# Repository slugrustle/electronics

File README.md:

# Electronics

This repository includes various electronics projects in a sufficient state of completion to publish informally.

HighImpedanceBuffer is a two&#x2011;channel unity gain buffer amplifier with high impedance inputs and a &#xb1;17.5V input range.

SOT23ZenerTester is a fixture and set of software that can be used to obtain the voltage / current curves of SOT23&#x2011;3 case Zener diodes when used in conjunction with other test equipment.

TestSequencer is a fairly simple board that surrounds an 8&#x2011;bit PIC microcontroller with a power supply, programming header, and various inputs and outputs through ESD protected terminal blocks. I use it for controlling other equipment and running tests.

HH509R\_Logger is a command line program to log temperature measurements from an Omega Engineering HH509R thermocouple reader.

Big\_Fast\_Switch is a sizable combination of film capacitor, N-MOSFET, and rectifier intended for generating input voltage transients to test DC->DC converters.

## Getting Started

The README files the individual directories descibed above are a good place to start.

## Contributing

I would love to receive bug reports and user feedback. If you have improvements to the code, please get in touch.

## Author

Ben Tesch &#x2013; [slugrustle](https://github.com/slugrustle)

## License

All files in this repository that have been produced by the author are distributed under the [CC0 1.0 Universal Public Domain Dedication](https://creativecommons.org/publicdomain/zero/1.0/). See also LICENSE.txt in each project directory and the files themselves.

The projects in this repository store copies of datasheets for parts used in each project. These remain under the copyright of their respective owners and are provided for reference.

The SOT23ZenerTester project also includes copies of files from the redistributable software for the Diolan DLN&#x2011;4ME interface adapter. These files belong to Diolan; see https://diolan.com for more information.

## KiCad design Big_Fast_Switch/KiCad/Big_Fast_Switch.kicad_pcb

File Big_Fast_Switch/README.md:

## Big\_Fast\_Switch

This project is a single-board assembly containing the following power electronic devices

- Large, high-voltage film capacitor (B32756G8156K000)
- High-voltage, low Rds(on), wide SOA N-Channel MOSFET (STY145N65M5)
- High-voltage, high-current fast rectifier (VS-90EPF06L-M3)

and the following support electronics / devices

- An isolated gate driver for the N-MOSFET
- Input logic (3.3V level, 5V tolerant) to control the N-MOSFET
- Independent heatsinks, fans, and temperature sensors for the N-MOSFET and Rectifier
- Overtemperature detection and latch circuitry that opens the N-MOSFET if either the N-MOSFET or Rectifier exceeds a temperature limit
- Separate AC->DC power supplies for the gate drive voltage supply (floating) and for the input logic, overtemperature circuitry, and cooling fans

This assembly was designed to aid in generating input voltage transients for the testing of DC->DC power supplies, but it could perhaps find other uses.

WARNING: Dangerous high voltages are present on this board including AC line voltage and high DC voltages. The construction or operation of this device is solely at your own risk. Do not attempt unless you are competent to personally evaluate the safety of high voltage electronic systems.

### Other Info

- Pictures of an assembled unit are available in the root of this repository.
- Design files for the board and schematic (as well as PDF / SVG printouts) are stored in the KiCad directory. I ordered the boards from PCBWay as 4-layer FR-4 boards with 3oz copper on all layers.
- STL files for a PCB holder and mounts for the cooling fans are available in the OpenSCAD directory. I printed these with flame retardant ABS filament.
- A full bill of materials can be found in the Bill\_of\_Materials directory.
- I attempted to save datasheets for all utilized components in the Datasheets directory.
- An LTspice simulation of the overtemperature detection and latch circuitry can be found in the Simulation directory. There are ancillary files from my attempt to create a reasonable model of the APT2012SURCK red LED.
- See LICENSE.txt for licensing info. I have endeavored to clarify which data stored here is my own work and which data belongs to others; all work that is my own is released under the CC0 1.0 Universal Public Domain Dedication.

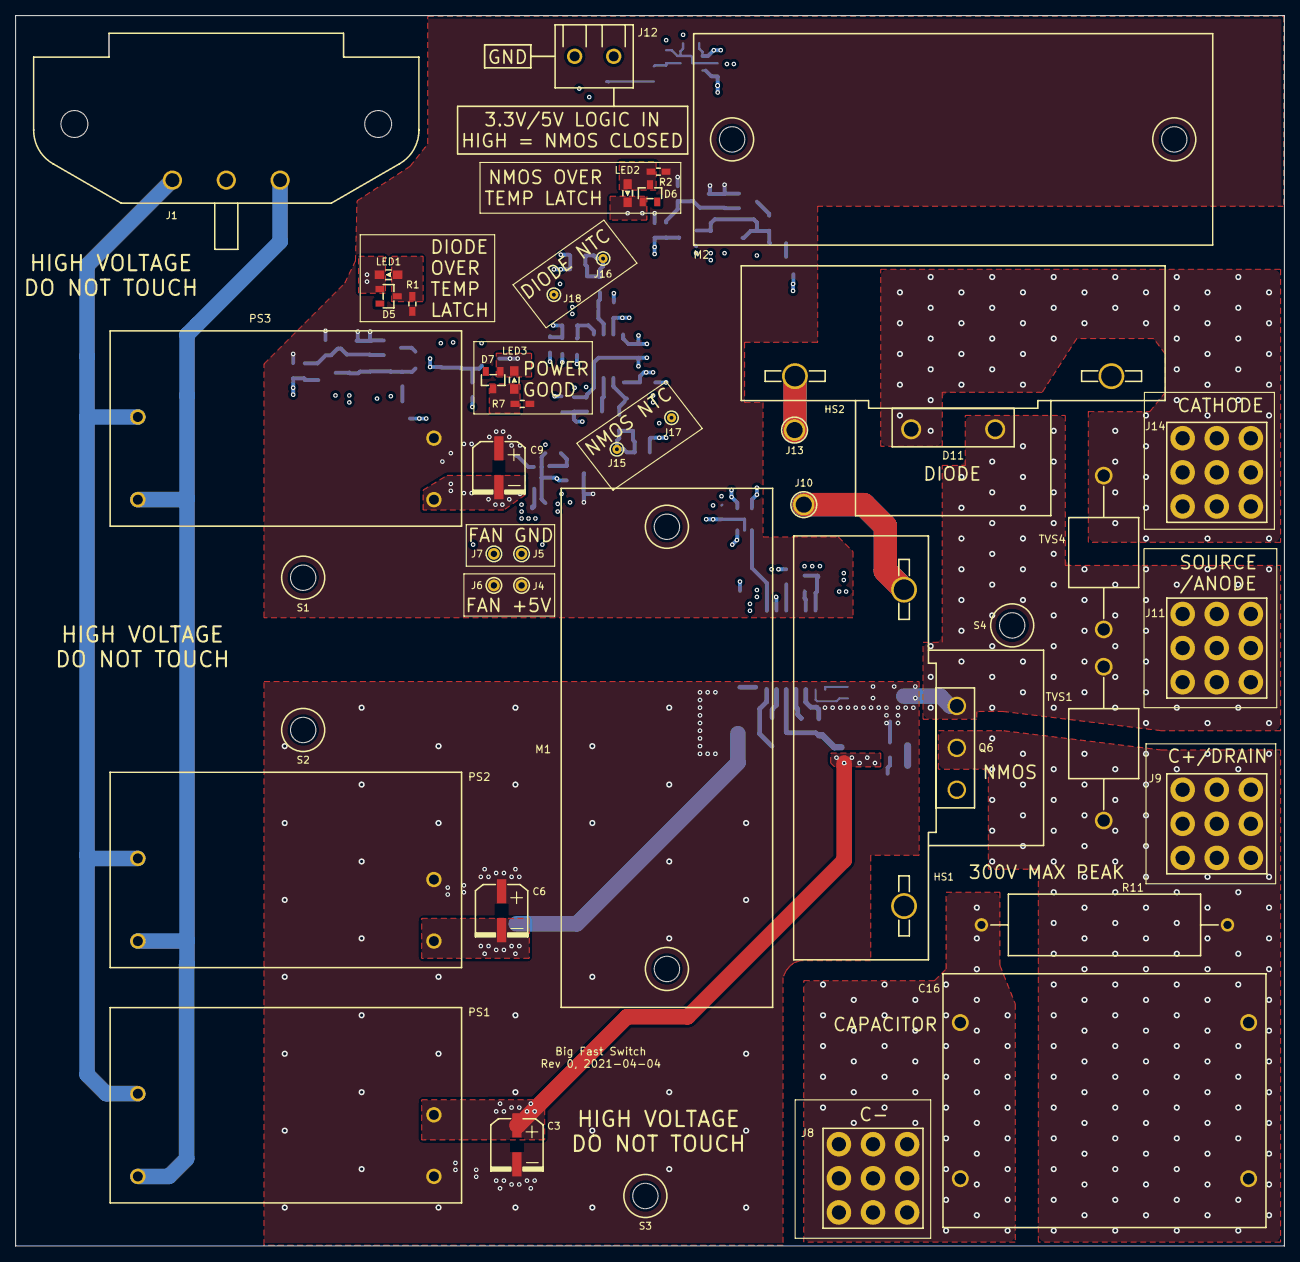
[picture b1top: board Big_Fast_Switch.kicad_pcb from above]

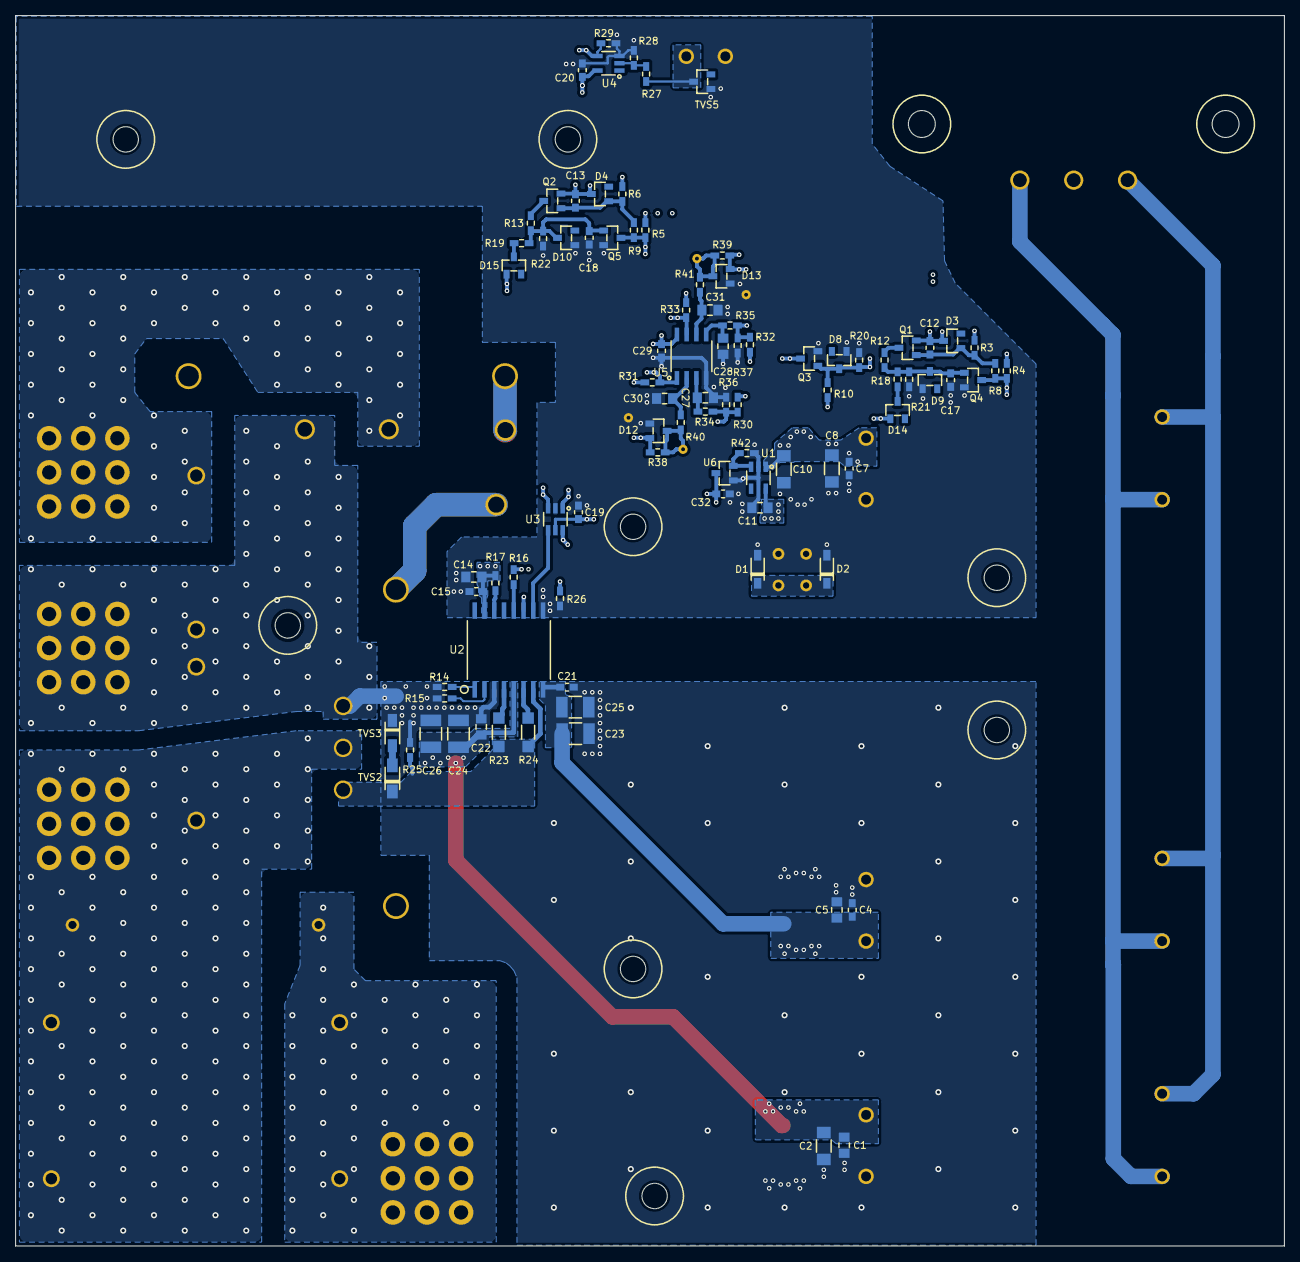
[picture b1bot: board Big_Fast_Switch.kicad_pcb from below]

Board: 4 copper layers, 165.0 x 160.0 mm, 136 parts (91 on the bottom side), 52 nets.

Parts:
C1, C22: 100n; C0805
C2, C8, C10: 2.2u; C1206
C3, C6, C9: 25SVPF47M; SVPF_C26
C4, C7, C15, C19, C20, C21, C29, C32: 100n; C0603
C5, C11, C14: 2.2u; C0805
C12, C13, C17, C18: 10n; C0603
C16: B32756G8156K000; B32756G
C23, C24, C25, C26: 10u; C1210
C27, C28: 4.7u; C0805
C30, C31: 1u; C0805
D1, D2: 1N4448W; SOD-123
D3, D4, D5, D6, D7, D8, D9, D10: BAS16; SOT-23-3
D11: VS-90EPF06L-M3; TO-247AD_2L
D12, D13: BAV199; SOT-23-3
D14, D15: BAS70; SOT-23-3
HS1, HS2: PA-T21-38E
J1: 703W-00-52
J4, J5, J6, J7: 26AWG_Stranded
J8, J9, J11, J14: 74651194R
J10, J13: 16AWG_Stranded
J12: 282837-2
J15, J16, J17, J18: 30AWG_Solid
LED1, LED2, LED3: APT2012SURCK
M1, M2: Fan_Mount
PS1: MPM-05-15; MPM-05
PS2: MPM-05-3.3; MPM-05
PS3: MPM-05-5; MPM-05
Q1, Q2: MMBT3906; SOT-23-3
Q3, Q4, Q5: MMBT3904; SOT-23-3
Q6: STY145N65M5; MAX247
R1, R2, R7: 620; R0603
R3, R6, R21, R22: 33k; R0603
R4, R5, R25, R34, R35, R40, R41: 10k; R0603
R8, R9: 43k; R0603
R10: 3.9k; R0603
R11: 47k; ROX5S
R12, R13: 6.2k; R0603
R14, R15: 100; R0603
R16, R27: 22; R0603
R17, R26: 1k; R0603
R18, R19: 2.7k; R0603
R20: 56k; R0603
R23: 2.7; R1206
R24: 1; R1206
R28, R29, R42: 100k; R0603
R30, R32, R36, R37, R38, R39: 523; R0603
R31, R33: 7.5k; R0603
S1, S2, S3, S4: Screw_#4
TVS1, TVS4: 30KPA300CA; 30KPA_Bidir
TVS2: SMF15A-E3-08; SMF
TVS3: PTVS3V3S1UR; SOD-123W
TVS5: DLP05LC; SOT-23-3
U1: MIC5225-3.3YM5; SOT-23-5
U2: UCC21750; UCC21750DW
U3: SN74LVC1G11DBVR; SOT-23-6
U4: SN74LVC1G17DBVR; SOT-23-5
U5: LMV762MA; SOIC-8
U6: TPS3839G33DBZR; SOT-23-3

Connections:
/3V3: C11.2, C14.2, C15.2, C19.1, C20.1, C29.1, D12.2, D13.2, R10.1, R17.1, R30.1, R32.1, R38.1, R39.1, U1.5, U2.15, U3.5, U4.5, U5.8
/5V: C7.2, C8.2, C9.1, C10.2, C12.2, C13.2, C32.2, D1.1, D2.1, D3.3, D4.3, J4.1, J6.1, PS3.4, Q1.2, Q2.2, R1.1, R2.1, R3.1, R4.1, R5.1, R6.1, R7.1, U1.1, U6.3
/15V: C1.2, C2.2, C3.1, C22.2, C24.2, C26.2, PS1.4, U2.5
/-3V3: C4.1, C5.1, C6.2, C21.1, C23.1, C25.1, PS2.3, U2.8
/C+_Drain: C16.2, J9.1, Q6.2, R11.2, TVS1.1
/C-: C16.1, J8.1, R11.1
/Cathode: D11.1, J14.1, TVS4.2
/OT_DIODE: D14.1, R33.1, U5.7
/OT_NMOS: D15.1, R31.1, U5.1
/~DIODE_LATCH: D5.1, LED1.1, Q4.3, R4.2, R8.2, U3.6
/~NMOS_LATCH: D6.1, LED2.1, Q5.3, R5.2, R9.2, U3.1
GND1: C7.1, C8.1, C9.2, C10.1, C11.1, C14.1, C15.1, C17.1, C18.1, C19.2, C20.2, C27.1, C28.1, C29.2, C30.1, C31.1, C32.1, D1.2, D2.2, D8.1, D9.1, D10.1, D12.1, D13.1, J5.1, J7.1, J12.2, J17.1, J18.1, PS3.3, Q3.2, Q4.2, Q5.2, R20.2, R21.2, R22.2, R26.2, R28.2, R29.2, R36.2, R37.2, R42.2, TVS5.1, U1.2, U2.9, U3.2, U4.3, U5.4, U6.1
GND2: C1.1, C2.1, C3.2, C4.2, C5.2, C6.1, C21.2, C22.1, C23.2, C24.1, C25.2, C26.1, D11.2, J11.1, PS1.3, PS2.4, Q6.3, R14.1, R15.1, R25.2, TVS1.2, TVS3.1, TVS4.1, U2.3
unnamed: C12.1, D3.1, Q1.1, R3.2, R8.1
unnamed: C13.1, D4.1, Q2.1, R6.2, R9.1
unnamed: C17.2, D9.3, Q4.1, R12.2, R18.1, R21.1
unnamed: C18.2, D10.3, Q5.1, R13.2, R19.1, R22.1
unnamed: C27.2, R34.1, U5.3
unnamed: C28.2, R35.1, U5.5
unnamed: C30.2, R40.1, U5.2
unnamed: C31.2, R41.1, U5.6
unnamed: D5.3, LED1.2, R1.2
unnamed: D6.3, LED2.2, R2.2
unnamed: D7.1, LED3.1, Q3.3
unnamed: D7.3, LED3.2, R7.2
unnamed: D8.3, Q3.1, R10.2, R16.2, R20.1
unnamed: D12.3, J15.1, R38.2, R40.2
unnamed: D13.3, J16.1, R39.2, R41.2
unnamed: D14.3, R18.2
unnamed: D15.3, R19.2
unnamed: HS1.2, J10.1
unnamed: HS2.1, J13.1
unnamed: J1.1, PS1.1, PS2.1, PS3.1
unnamed: J1.3, PS1.2, PS2.2, PS3.2
unnamed: J12.1, R27.2, TVS5.3
unnamed: Q1.3, R12.1
unnamed: Q2.3, R13.1
unnamed: Q6.1, R23.1, R24.1, R25.1, TVS2.1, U2.7
unnamed: R14.2, U2.1
unnamed: R15.2, U2.2
unnamed: R16.1, U2.12
unnamed: R17.2, U2.14
unnamed: R23.2, U2.4
unnamed: R24.2, U2.6
unnamed: R26.1, U2.11
unnamed: R27.1, R28.1, U4.2
unnamed: R29.1, U3.3, U4.4
unnamed: R30.2, R31.2, R34.2, R36.1
unnamed: R32.2, R33.2, R35.2, R37.1
unnamed: R42.1, U1.3, U6.2
unnamed: TVS2.2, TVS3.2
unnamed: U2.10, U3.4

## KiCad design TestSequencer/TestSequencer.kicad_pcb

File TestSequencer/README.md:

## Test Sequencer

This project surrounds an 8&#x2011;bit PIC microcontroller (PIC16F15324) with

1. Power supply from a DC barrel jack with both ESD and reverse polarity protection. A 5V linear regulator runs the MCU and output buffers.
2. A 32MHz external oscillator
3. A 6p6c modular jack with ESD protection for ICSP programming with an ICD3 or ICD4
4. 7 32mA capable logic&#x2011;level output buffers broken out to terminal blocks with ESD protection
5. An input for a toggle switch or pushbutton broken out to a terminal block with ESD protection
6. A slightly hacky but functional enclosure

After many times wanting to write some very basic assembly code to debounce a button and generate some simple logic&#x2011;level waveforms
to control other equipment or directly interface with a circuit under test, I decided to build a board to serve this role.

The PIC16F15324 was chosen primarily out of familiarity but also for its reasonable specs and capability (relative to this application) and for having no serious errata.

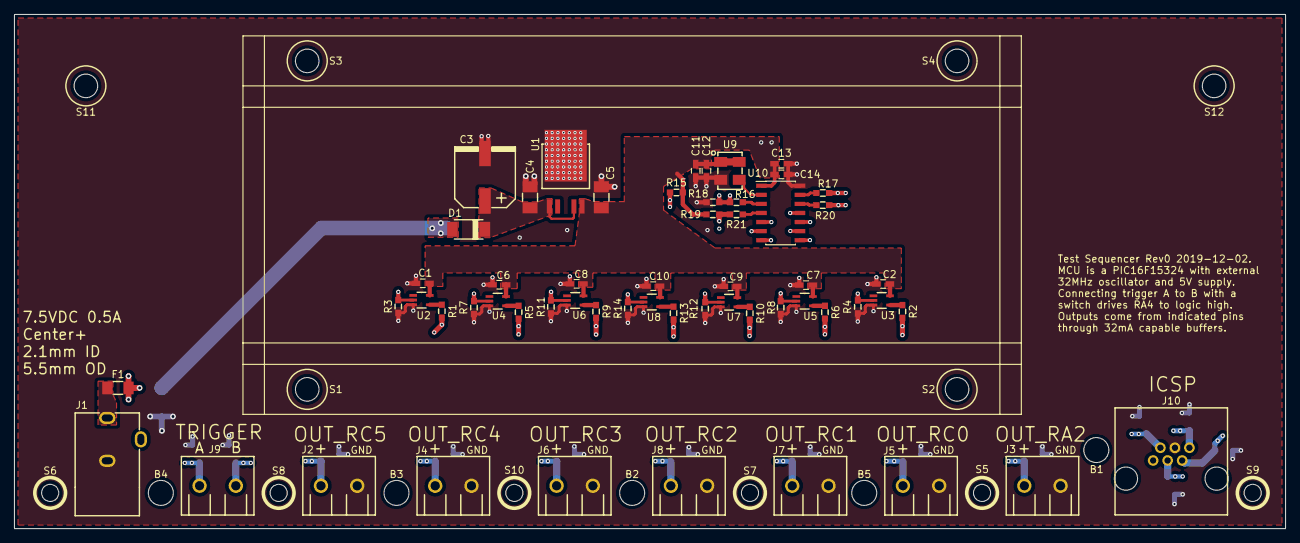
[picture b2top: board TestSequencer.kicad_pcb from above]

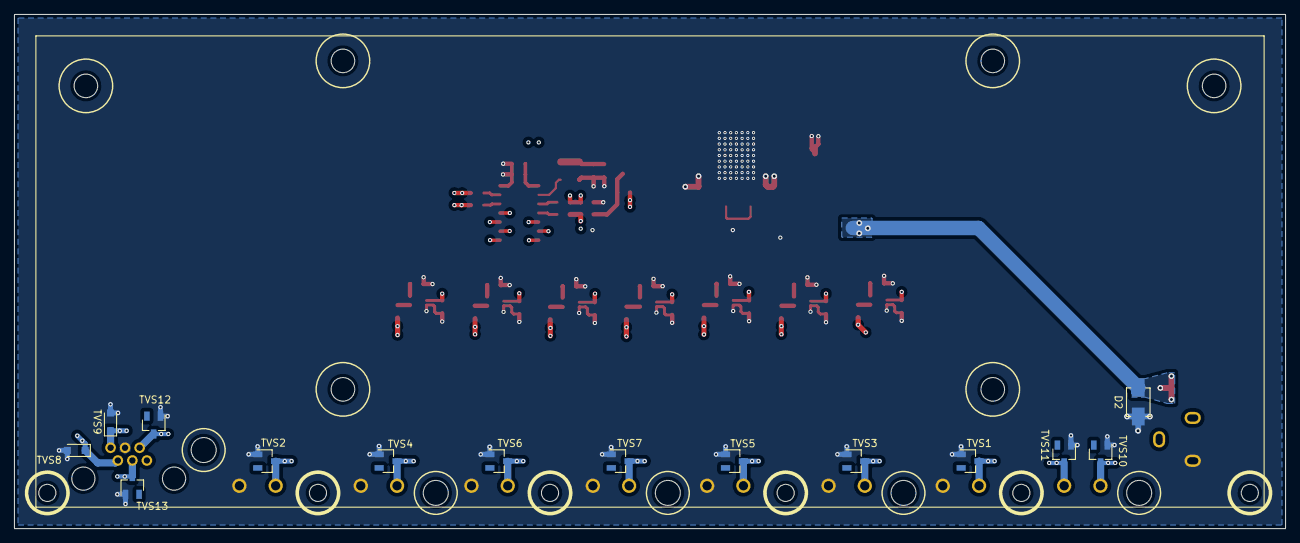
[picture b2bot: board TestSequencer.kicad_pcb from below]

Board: 4 copper layers, 178.0 x 72.0 mm, 88 parts (14 on the bottom side), 36 nets.

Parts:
B1, B2, B3, B4, B5: MountingBoss
C1, C2, C6, C7, C8, C9, C10, C11, C13: 100n; C_0603_HandSoldering
C3: HHXA500ARA470MHA0G; HXA_HA0
C4: 1u; C_1206
C5: 10u; C_1206
C12, C14: 10n; C_0603_HandSoldering
D1: PMEG60T10ELPX; SOD-128
D2: SMAJ15CA; D_SMA_Bidir
F1: 0685T1500-01; F_1206
J1: PJ-102AH
J2, J3, J4, J5, J6, J7, J8, J9: 282837-2
J10: 0438600002
R1, R2, R5, R6, R9, R10, R13: 10R; R_0603
R3, R4, R7, R8, R11, R12, R14: 47k; R_0603
R15: 220R; R_0603
R16, R19: 10k; R_0603
R17, R20, R21: 22R; R_0603
R18: 2.4k; R_0603
S1, S2, S3, S4, S11, S12: Screw_#4
S5, S6, S7, S8, S9, S10: Screw_#2
TVS1, TVS2, TVS3, TVS4, TVS5, TVS6, TVS7, TVS10, TVS11, TVS12, TVS13: DLP05LC-7-F; SOT-23
TVS8: SD05-7; D_SOD-323_HandSoldering
TVS9: DF2S12FU,H3F; D_SOD-323_HandSoldering
U1: IFX24401TEV50; IFX24401TEV
U2, U3, U4, U5, U6, U7, U8: NL17SZ17DFT2G; SC-70-5
U9: KC5032A32.0000CMGE00; KC5032A-CM
U10: PIC16F15324-E_SN; SOIC-14_3.9x8.7mm_Pitch1.27mm

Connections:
/5V: C1.1, C2.1, C5.1, C6.1, C7.1, C8.1, C9.1, C10.1, C11.1, C12.1, C13.2, C14.2, J10.2, R15.2, R19.1, TVS8.1, U1.5, U2.5, U3.5, U4.5, U5.5, U6.5, U7.5, U8.5, U9.1, U9.4, U10.1
/J_PGC: J10.5, R20.1, TVS12.3
/J_PGD: J10.4, R17.1, TVS13.3
/J_VPP: J10.1, R19.2, R21.2, TVS9.1
/OUT_RA2: R4.2, U3.2, U10.11
/OUT_RC0: R8.2, U5.2, U10.10
/OUT_RC1: R12.2, U7.2, U10.9
/OUT_RC2: R14.2, U8.2, U10.8
/OUT_RC3: R11.2, U6.2, U10.7
/OUT_RC4: R7.2, U4.2, U10.6
/OUT_RC5: R3.2, U2.2, U10.5
GND: C1.2, C2.2, C3.2, C4.2, C5.2, C6.2, C7.2, C8.2, C9.2, C10.2, C11.2, C12.2, C13.1, C14.1, D2.2, J1.2, J2.2, J3.2, J4.2, J5.2, J6.2, J7.2, J8.2, J10.3, R3.1, R4.1, R7.1, R8.1, R11.1, R12.1, R14.1, R18.2, TVS1.1, TVS2.1, TVS3.1, TVS4.1, TVS5.1, TVS6.1, TVS7.1, TVS8.2, TVS9.2, TVS10.1, TVS11.1, TVS12.1, TVS13.1, U1.3, U2.3, U3.3, U4.3, U5.3, U6.3, U7.3, U8.3, U9.2, U10.14
unnamed: C3.1, C4.1, D1.1, U1.1, U1.4
unnamed: D1.2, D2.1, F1.1
unnamed: F1.2, J1.1
unnamed: J2.1, R1.1, TVS1.3
unnamed: J3.1, R2.1, TVS2.3
unnamed: J4.1, R5.1, TVS3.3
unnamed: J5.1, R6.1, TVS4.3
unnamed: J6.1, R9.1, TVS5.3
unnamed: J7.1, R10.1, TVS6.3
unnamed: J8.1, R13.1, TVS7.3
unnamed: J9.1, R15.1, TVS10.3
unnamed: J9.2, R16.1, R18.1, TVS11.3
unnamed: R1.2, U2.4
unnamed: R2.2, U3.4
unnamed: R5.2, U4.4
unnamed: R6.2, U5.4
unnamed: R9.2, U6.4
unnamed: R10.2, U7.4
unnamed: R13.2, U8.4
unnamed: R16.2, U10.3
unnamed: R17.2, U10.13
unnamed: R20.2, U10.12
unnamed: R21.1, U10.4
unnamed: U9.3, U10.2

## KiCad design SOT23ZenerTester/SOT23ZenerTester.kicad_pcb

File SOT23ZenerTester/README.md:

## Fixture and Software for Testing SOT23&#x2011;3 Zener Diodes

This project includes a circuit board designed to obtain the voltage / current characteristics
of SOT23&#x2011;3 package Zener diodes when used in conjunction with the following test equipment:

1. A Diolan DLN&#x2011;4ME interface adapter to control the fixture board relays for selecting the Zener diode and pullup resistor to use in testing
2. An ITECH IT6100B series power supply (the IT6123B is a good choice) to bias the Zener diode under test via the selected fixture pullup resistor
3. A Rigol DM3068 digital multimeter to measure the Zener diode cathode voltage when the diode is biased
4. A PC with at least 1 USB2 port (for the Diolan DLN&#x2011;4ME) and at least 2 RS232 ports (for the power supply and DMM)

This project also includes software to control the test equipment, calculate the Zener diode voltage / current characteristics from measurement data, and output the results in a .xlsx workbook.

Many elements of the test setup can be specified in a text&#x2011;based configuration file; examples of these can be found in the FixtureProgram/Release directory. There are two test programs: TestZeners, which obtains a full voltage / current curve, and SingleShot, which measures the Zener diode voltage / current at a single fixture setting after a \~1ms delay. Example output files for each program can be found in the FixtureProgram/Release directory.

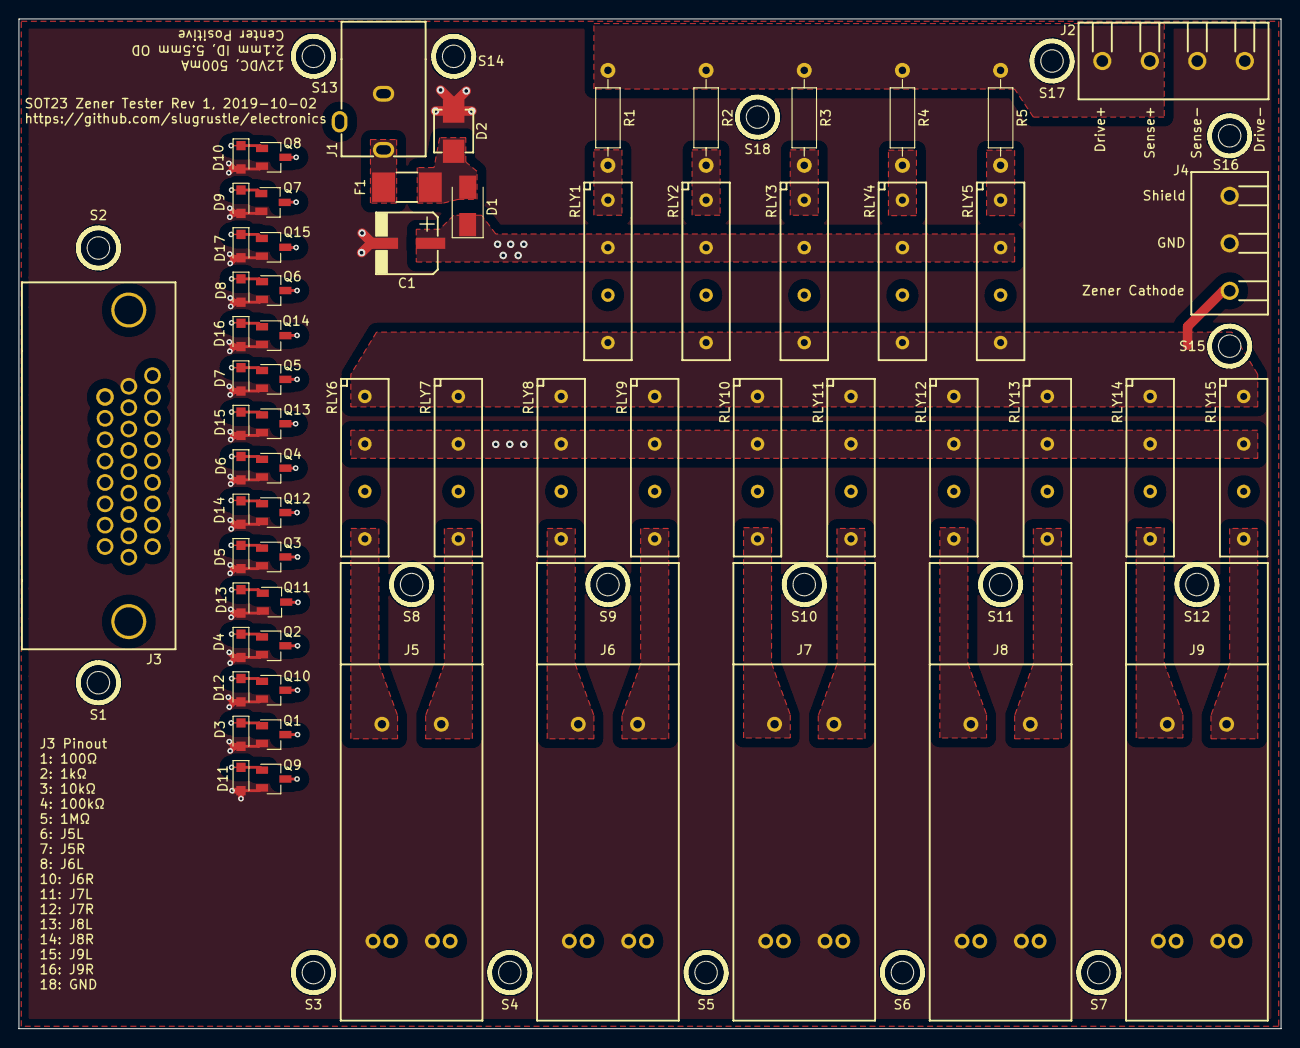
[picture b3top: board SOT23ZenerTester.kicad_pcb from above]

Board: 4 copper layers, 135.0 x 108.0 mm, 81 parts (0 on the bottom side), 51 nets.

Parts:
C1: HHXC350ARA680MF80G; HHXC_F80
D1: NRVTSA4100E; D_SMA
D2: SMBJ13CA; D_SMB_Bidir
D3, D4, D5, D6, D7, D8, D9, D10, D11, D12, D13, D14, D15, D16, D17: PESD5V0L1UA; D_SOD-323_HandSoldering
F1: 0679L0375-05; Fuse_2410
J1: PJ-102AH
J2: 282837-4
J3: L17HTHAS4F1C
J4: 282837-3
J5, J6, J7, J8, J9: CSD_Dual_SOT23; CSD_Technology_Dual_SOT23_ZIF
Q1, Q2, Q3, Q4, Q5, Q6, Q7, Q8, Q9, Q10, Q11, Q12, Q13, Q14, Q15: PDTC123JT; SOT-23
R1: 100; R_Axial_DIN0207_L6.3mm_D2.5mm_P10.16mm_Horizontal
R2: 1k; R_Axial_DIN0207_L6.3mm_D2.5mm_P10.16mm_Horizontal
R3: 10k; R_Axial_DIN0207_L6.3mm_D2.5mm_P10.16mm_Horizontal
R4: 100k; R_Axial_DIN0207_L6.3mm_D2.5mm_P10.16mm_Horizontal
R5: 1M; R_Axial_DIN0207_L6.3mm_D2.5mm_P10.16mm_Horizontal
RLY1, RLY2, RLY3, RLY4, RLY5, RLY6, RLY7, RLY8, RLY9, RLY10, RLY11, RLY12, RLY13, RLY14, RLY15: 3570-1331-123
S1, S2, S3, S4, S5, S6, S7, S8, S9, S10, S11, S12, S13, S14, S15, S16, S17, S18: Screw_#2

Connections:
/12V: C1.1, D1.1, RLY1.2, RLY2.2, RLY3.2, RLY4.2, RLY5.2, RLY6.2, RLY7.2, RLY8.2, RLY9.2, RLY10.2, RLY11.2, RLY12.2, RLY13.2, RLY14.2, RLY15.2
/R1KRLY: D4.1, J3.2, Q2.1
/R1MRLY: D7.1, J3.5, Q5.1
/R10KRLY: D5.1, J3.3, Q3.1
/R100KRLY: D6.1, J3.4, Q4.1
/R100RLY: D3.1, J3.1, Q1.1
/VSWEEP: J2.3, J2.4, R1.1, R2.1, R3.1, R4.1, R5.1
/ZD1RLY: D8.1, J3.6, Q6.1
/ZD2RLY: D9.1, J3.7, Q7.1
/ZD3RLY: D10.1, J3.8, Q8.1
/ZD4RLY: D11.1, J3.10, Q9.1
/ZD5RLY: D12.1, J3.11, Q10.1
/ZD6RLY: D13.1, J3.12, Q11.1
/ZD7RLY: D14.1, J3.13, Q12.1
/ZD8RLY: D15.1, J3.14, Q13.1
/ZD9RLY: D16.1, J3.15, Q14.1
/ZD10RLY: D17.1, J3.16, Q15.1
/Z_Cathode: J4.1, RLY1.4, RLY2.4, RLY3.4, RLY4.4, RLY5.4, RLY6.1, RLY7.1, RLY8.1, RLY9.1, RLY10.1, RLY11.1, RLY12.1, RLY13.1, RLY14.1, RLY15.1
GND: C1.2, D2.2, D3.2, D4.2, D5.2, D6.2, D7.2, D8.2, D9.2, D10.2, D11.2, D12.2, D13.2, D14.2, D15.2, D16.2, D17.2, J1.2, J2.1, J2.2, J3.18, J4.2, J4.3, J5.1, J5.4, J6.1, J6.4, J7.1, J7.4, J8.1, J8.4, J9.1, J9.4, Q1.2, Q2.2, Q3.2, Q4.2, Q5.2, Q6.2, Q7.2, Q8.2, Q9.2, Q10.2, Q11.2, Q12.2, Q13.2, Q14.2, Q15.2
unnamed: D1.2, D2.1, F1.1
unnamed: F1.2, J1.1
unnamed: J5.3, RLY6.4
unnamed: J5.6, RLY7.4
unnamed: J6.3, RLY8.4
unnamed: J6.6, RLY9.4
unnamed: J7.3, RLY10.4
unnamed: J7.6, RLY11.4
unnamed: J8.3, RLY12.4
unnamed: J8.6, RLY13.4
unnamed: J9.3, RLY14.4
unnamed: J9.6, RLY15.4
unnamed: Q1.3, RLY1.3
unnamed: Q2.3, RLY2.3
unnamed: Q3.3, RLY3.3
unnamed: Q4.3, RLY4.3
unnamed: Q5.3, RLY5.3
unnamed: Q6.3, RLY6.3
unnamed: Q7.3, RLY7.3
unnamed: Q8.3, RLY8.3
unnamed: Q9.3, RLY9.3
unnamed: Q10.3, RLY10.3
unnamed: Q11.3, RLY11.3
unnamed: Q12.3, RLY12.3
unnamed: Q13.3, RLY13.3
unnamed: Q14.3, RLY14.3
unnamed: Q15.3, RLY15.3
unnamed: R1.2, RLY1.1
unnamed: R2.2, RLY2.1
unnamed: R3.2, RLY3.1
unnamed: R4.2, RLY4.1
unnamed: R5.2, RLY5.1

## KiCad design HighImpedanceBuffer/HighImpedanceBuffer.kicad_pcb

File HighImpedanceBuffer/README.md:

## 2&#x2011;Channel High Input Impedance Unity&#x2011;Gain Buffer Amplifier

This project is a 2&#x2011;channel unity&#x2011;gain buffer amplifier built around the Texas Instruments OPA192. The amplifier inputs have ESD protection and high input impedance. The amplifier will behave normally with up to &#xb1;17.5V signal on its inputs. It is powered from a 20VAC 200mA supply such as the Triad Magnetics WAU20&#x2011;200 or similar.

There is a 120&#x3a9; impedance inside the amplifier feedback loop after the internal opamp output pin which limits the output voltage range at heavier output loads. Due to this phenomenon and the thermal characteristics of the voltage regulators, it is recommended that the impedance of the load applied to the output of each amplifier be 1.1k&#x3a9; or higher.

To maintain high input impedance, there is no resistance biasing the external amplifier inputs to GND in a default state. Consequently, if a channel is unused, it is recommended to connect IN to COM (or GND) for that channel.

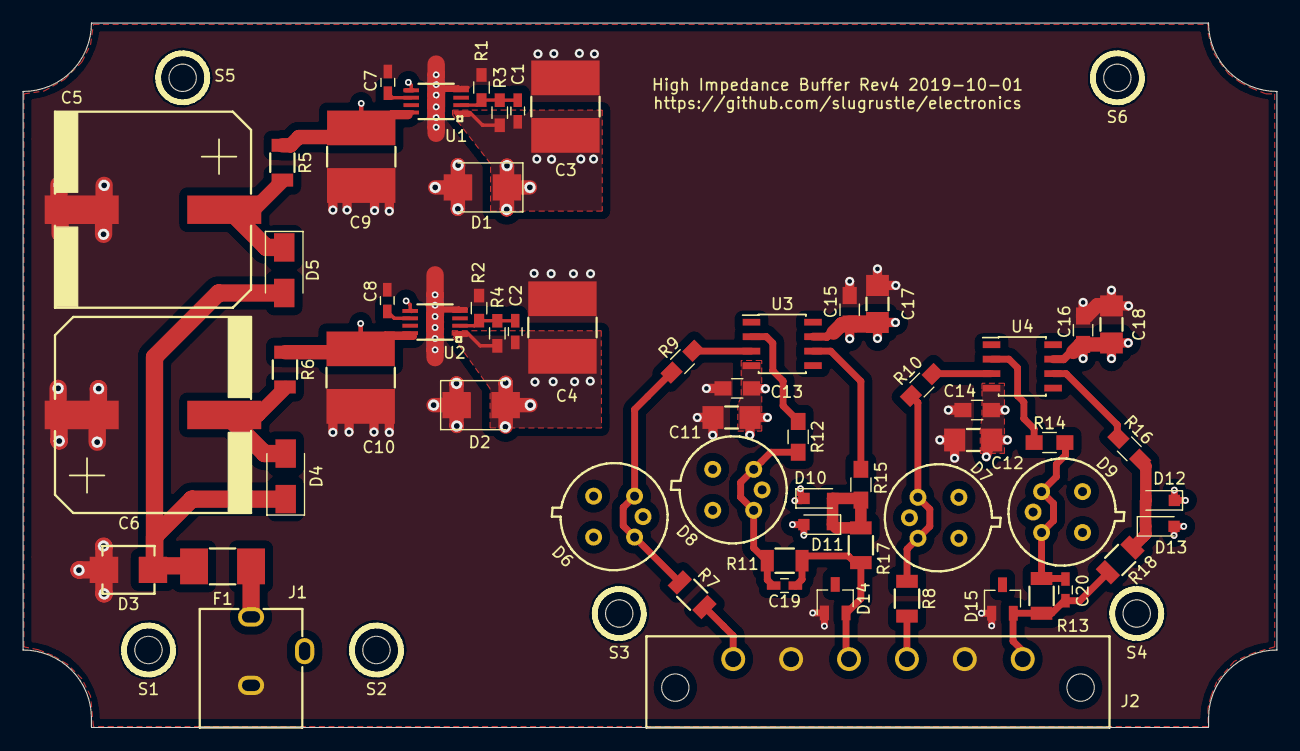
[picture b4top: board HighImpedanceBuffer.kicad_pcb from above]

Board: 4 copper layers, 110.0 x 61.8 mm, 66 parts (0 on the bottom side), 29 nets.

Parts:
C1, C2, C7, C8: 10n_NP0; C_0603_HandSoldering
C3, C4, C9, C10: 10u; C_2220
C5, C6: 470u; TG_J16
C11, C12, C17, C18: 1u; C_1206
C13, C14, C15, C16: 100n; C_0805_HandSoldering
C19, C20: TBD; C_0603_HandSoldering
D1, D2: SMBJ18A; D_SMB
D3: SMBJ36CA; D_SMB_Bidir
D4, D5: NRVTSA4100E; D_SMA
D6, D7, D8, D9: DPAD1; TO-78-5
D10, D11, D12, D13: CMDD6001; D_SOD-323_HandSoldering
D14, D15: MMBZ27VAL; SOT-23
F1: SF-2410FP0375T-2; Fuse_2410
J1: PJ-102AH
J2: 1776540
R1, R2: 6.2k; R_0603_HandSoldering
R3, R4: 88.7k; R_0603_HandSoldering
R5, R6: 2.2; R_1206
R7, R8: 10k; R_1206
R9, R10, R12, R14: 1k; R_0805_HandSoldering
R11, R13: 2.7k; R_1206
R15, R16: 20; R_0805_HandSoldering
R17, R18: 100; R_1206
S1, S2, S3, S4, S5, S6: Screw_#2
U1: TPS7A4901DGNR; MSOP-8-EP
U2: TPS7A3001DGNR; MSOP-8-EP
U3, U4: OPA192IDR; SOIC-8_3.9x4.9mm_Pitch1.27mm

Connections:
/18V+: C1.1, C3.2, C15.2, C16.2, C17.2, C18.2, D1.1, D6.1, D7.1, D8.1, D9.1, D10.1, D12.1, R3.1, U1.1, U3.7, U4.7
/18V-: C2.1, C4.2, C11.1, C12.1, C13.1, C14.1, D2.2, D6.7, D7.7, D8.7, D9.7, D11.2, D13.2, R4.1, U2.1, U3.4, U4.4
/IN1: J2.1, R7.2
/IN2: J2.4, R8.2
/OUT1: C19.1, D14.2, J2.3, R11.1, R17.1
/OUT2: C20.1, D15.2, J2.6, R13.1, R18.1
/PreReg+: C9.1, R5.1, U1.5, U1.8
/PreReg-: C10.2, R6.1, U2.5, U2.8
GND: C3.1, C4.1, C5.2, C6.1, C7.2, C8.2, C9.2, C10.1, C11.2, C12.2, C13.2, C14.2, C15.1, C16.1, C17.1, C18.1, D1.2, D2.1, D3.2, D14.1, D15.1, J1.2, J2.2, J2.5, R1.2, R2.2, U1.4, U1.9, U2.4, U2.9
unnamed: C1.2, R1.1, R3.2, U1.2
unnamed: C2.2, R2.1, R4.2, U2.2
unnamed: C5.1, D5.1, R5.2
unnamed: C6.2, D4.2, R6.2
unnamed: C7.1, U1.6
unnamed: C8.1, U2.6
unnamed: C19.2, D8.3, D8.5, R11.2, R12.2
unnamed: C20.2, D9.3, D9.5, R13.2, R14.2
unnamed: D3.1, D4.1, D5.2, F1.1
unnamed: D6.3, D6.5, R7.1, R9.2
unnamed: D7.3, D7.5, R8.1, R10.2
unnamed: D10.2, D11.1, R15.1, R17.2
unnamed: D12.2, D13.1, R16.1, R18.2
unnamed: F1.2, J1.1
unnamed: R9.1, U3.3
unnamed: R10.1, U4.3
unnamed: R12.1, U3.2
unnamed: R14.1, U4.2
unnamed: R15.2, U3.6
unnamed: R16.2, U4.6

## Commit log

2019-09-01 First commit
    Most design files are present. Still need to design enclosure lid and add readme, license, user manual, etc.
2019-09-01 mechanical update
    Extended edge of board with connectors 0.8mm so the connector faces sit flush with the front of the enclosure.
2019-09-01 Adding license information
2019-09-15 Rev3, enclosure updates
    Rev3: Updating fuse for higher A^2s rating, fixing linear regulator footprint.
    Adding enclosure lid & label. Switching to 5/16" long screws for board. Updating diameter of hole for board screws so threads catch better.
2019-09-22 Adding SOT23 Zener Tester board
    Bill of Materials and CAD for board support plastic are still pending. This is a board for testing the reverse voltage / current curve of SOT23-3 package zener diodes using a programmable power suppl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
2019-10-02 HighImpedanceBuffer Rev4, SOT23ZenerTester BoM, plate
    Improved layout, resistor value changes, and added capacitors to solve oscillation problem in high impedance buffer. Added BoM and CAD for 3D printed support plate to SOT23 Zener Tester.
2019-10-03 SOT23 Zener Tester Rev1
    Fixing footprints of J2 and J4.
2019-11-16 initial commit
    Initial commit of a program that uses a SOT23ZenerTester board in conjunction with a Diolan DLN-4ME USB to GPIO/I2C/etc. Adapter, a Rigol DM3068 DMM, and an Itech 6100B serie PSU to measure the Volta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
    The program files still require proper file header comments, and various desired features are missing:
    1. I would like to have the configuration file parser ignore the UTF8 byte order mark if it appears in the configuration file. UTF8 text files are not supposed to use the byte order mark, but Windows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
    2. The output Office Open XML workbook file does not have a
2019-11-16 Various updates/fixes
    Replaced MIN_RECORDABLE_CURRENT constant in TestZeners.cpp with MIN_VALID_ZENER_CURRENT configuration field. Actually implemented POWER_LIMITED argument for MAX_CURRENT_{Zener Socket Name} fields in 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
    Added an end of test console message.
2019-11-28 File reorganization, adding SingleShot test
    Reorganizing files so that files containing code shared between TestZeners and SingleShot are separated from files containing code specific to each test program.
    The SingleShot test sets up the power supply output voltage and closes the indicated test resistor relay before briefly closing the relay for each installed Zener diode, measuring the voltage, and op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
2020-02-15 adding TestSequencer
    README to follow later
2020-02-23 README, enclosure images, LICENSE touchup
    Finally adding a README file.
    Adding OpenSCAD image exports of the enclosure.
    Updating filenames and so forth in LICENSE.txt
2020-02-23 README updates
    Nothing like reading it through after committing.
2020-02-23 Adding README
    Adding a much needed README file.
    Touching up filenames in the LICENSE file.
    Adding a bottom assembly view, since this project does have some parts on the bottom of the PCB.
2020-02-24 Documentation updates
    Improving program file header comments, adding a README, and updating the file list in LICENSE.txt.
2020-06-26 First Commit
    Adding HH509R_Logger to the electronics repository.
2020-06-26 README update
    A bit of touching up.
2020-06-27 HH509R_Logger improvements
    1. More use of functions and fewer magic numbers.
    2. More comments (hopefully helpful).
    3. Added a mechanism that attempts to restart data collection if it stops.
    4. No longer putting the thermocouple reader in record mode; this appears to be unnecessary.
    5. Other minor touchups.
2020-06-29 Code cleanup, bad timestamp workaround
    Cleaned up the code some more:
    - Temperature format conversion is now in a function.
    - Using an enum to enumerate all possible commands to send to the thermocouple reader instead of constant strings.
    - Improved logic surrounding handling of incoming thermocouple reader data lines.
    Found a bug in the HH509R firmware: Timestamps past 9h 59m 59s device operation are invalid and contain a non-printable ASCII character. Since HH509R_Logger doesn't use the HH509R internal timestamps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
    Committing so this isn't just stored on my computer.
2020-06-30 Code cleanup / improvement
    Simply not validating the most significant minutes digit works much better, allows data collection beyond 11 hours.
    Improved the logic for keeping the thermocouple reader out of special modes.
    Put data line validation into its own function.
    Line similarity comparisons no longer look at status data, which may change between lines that are otherwise the same in their temperature and timestamp. This avoids throwing out good data.
    Updated BasicWorkbook so that the default cell type is general; this makes it so that formulas actually work when you type them into other cells.
    Still haven't updated example_data.xlsx. Still haven't removed diagnostic logging. Those wi
2020-07-02 Test Concluded
    Managed to log for 70 hours seemingly successfully. Removing diagnostic logging & updating example_data.xlsx.
2020-07-03 Readme update
    Adding HH509R_Logger to electronics repo top level readme.
2021-08-09 adding Big_Fast_Switch
    Adding the Big_Fast_Switch project and updating root readme.
2023-10-29 filename changes
    Removing odd unicode characters from filenames.

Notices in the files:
Big_Fast_Switch/KiCad/Big_Fast_Switch.kicad_pcb:
Published Under the CC0 1.0 Universal Public Domain Dedication
